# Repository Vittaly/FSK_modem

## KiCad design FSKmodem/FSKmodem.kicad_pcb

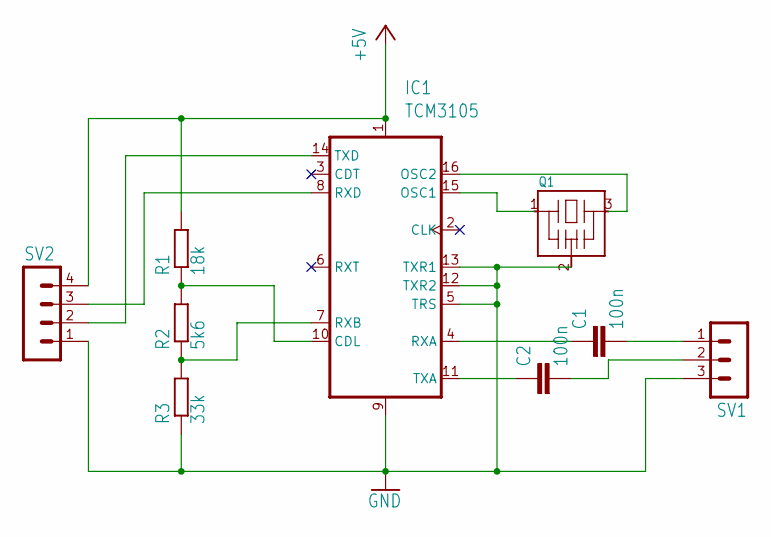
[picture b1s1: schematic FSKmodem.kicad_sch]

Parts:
C1, C2: 100n; C_1206_3216Metric_Pad1.33x1.80mm_HandSolder
IC1: TCM3105; DIP-16_W7.62mm
Q1: CSTLS_G; Resonator-3Pin_W6.0mm_H3.0mm
R1: 18k; R_1206_3216Metric_Pad1.30x1.75mm_HandSolder
R2: 5k6; R_1206_3216Metric_Pad1.30x1.75mm_HandSolder
R3: 33k; R_1206_3216Metric_Pad1.30x1.75mm_HandSolder
SV1: MA03-1; PinHeader_1x03_P2.54mm_Horizontal
SV2: MA04-1; PinHeader_1x04_P2.54mm_Horizontal

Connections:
+5V: IC1.1 (VDD), R1.2, SV2.4
GND: IC1.5 (TRS), IC1.9 (VSS), IC1.12 (TXR2), IC1.13 (TXR1), Q1.2 (VSS), R3.1, SV1.3, SV2.1
unnamed: C1.2, SV1.1
unnamed: C2.2, SV1.2
unnamed: IC1.10 (CDL), R1.1, R2.2
unnamed: IC1.15 (OSC1), Q1.1
unnamed: IC1.16 (OSC2), Q1.3
unnamed: C1.1, IC1.4 (RXA)
unnamed: IC1.7 (RXB), R2.1, R3.2
unnamed: IC1.8 (RXD), SV2.3
unnamed: C2.1, IC1.11 (TXA)
unnamed: IC1.14 (TXD), SV2.2

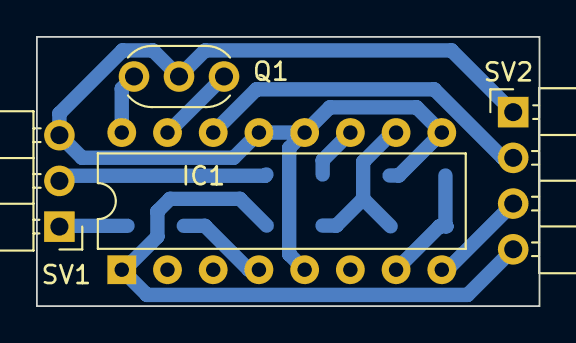
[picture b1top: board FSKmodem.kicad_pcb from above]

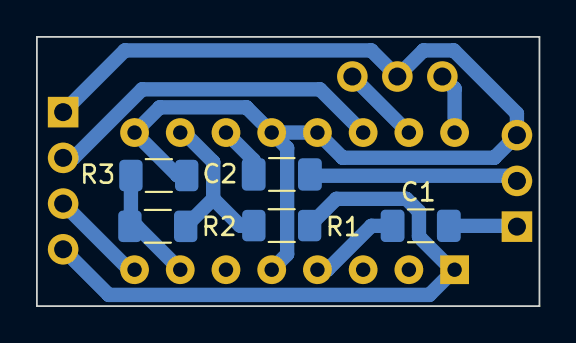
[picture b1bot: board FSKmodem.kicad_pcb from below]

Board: 2 copper layers, 27.9 x 15.0 mm, 9 parts (5 on the bottom side), 12 nets.

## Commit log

2023-11-12 create kicad project, use cmd resistors
2024-01-05 change zone filling
2024-01-05 drilling refrashed
2024-02-21 ready for lut
2024-02-21 some fix
